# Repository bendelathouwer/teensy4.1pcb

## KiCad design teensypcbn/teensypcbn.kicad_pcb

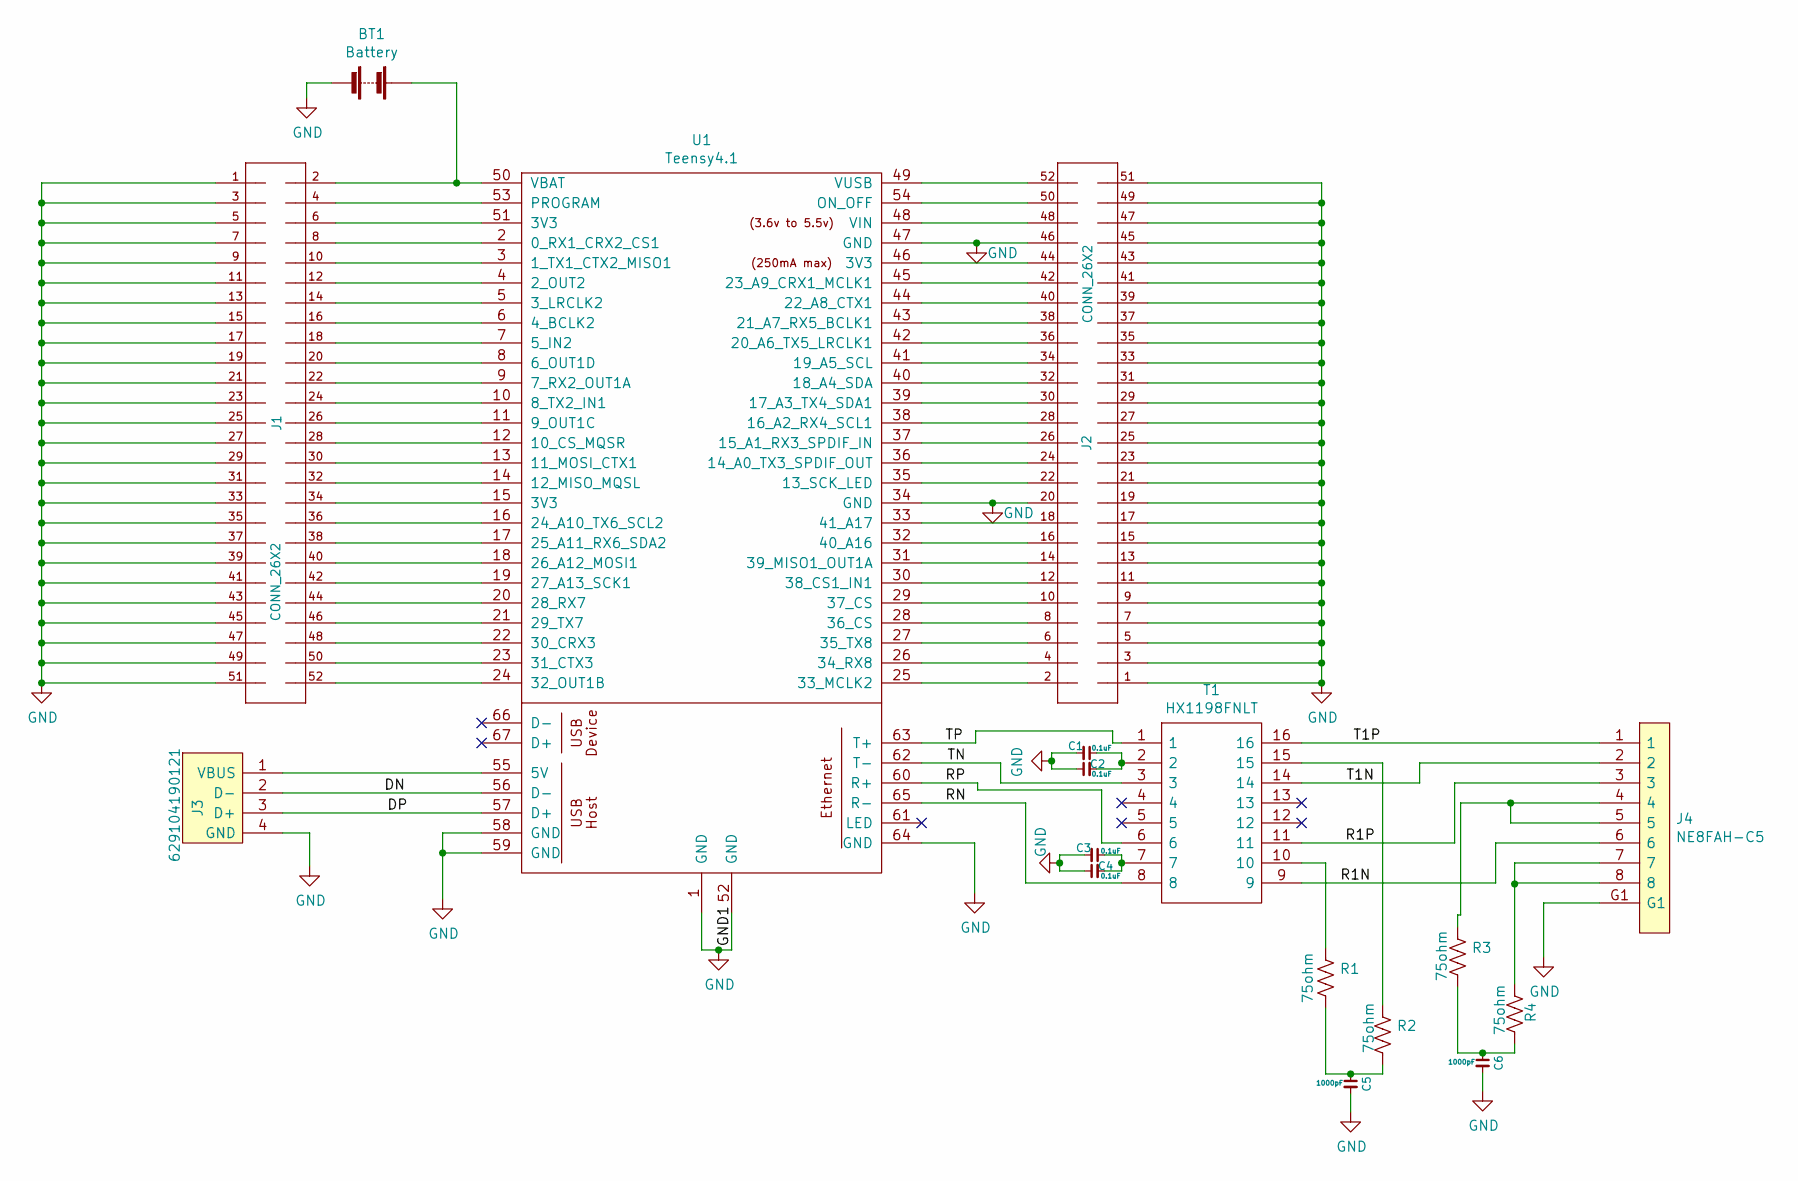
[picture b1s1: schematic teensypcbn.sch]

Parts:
BT1: Battery; JST_PH_B2B-PH-SM4-TB_1x02-1MP_P2.00mm_Vertical
C1, C2, C3, C4: 0.1uF; C_0603_1608Metric_Pad0.99x1.00mm_HandSolder
C5, C6: 1000pF; C_0603_1608Metric_Pad0.99x1.00mm_HandSolder
J1, J2: CONN_26X2; PinHeader_2x26_P2.54mm_Vertical
J3: 629104190121; Mouser Part Number 710-629104190121
J4: NE8FAH-C5; NE8FAHC5; Mouser Part Number 568-NE8FAH-C5
R1, R2, R3, R4: 75ohm; R_0603_1608Metric
T1: HX1198FNLT; Manufacturer_Part_Number HX1198FNLT; Mouser Part Number 673-HX1198FNLT
U1: Teensy4.1; Teensy41

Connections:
/DN: J3.2 (D-), U1.56 (D-)
/DP: J3.3 (D+), U1.57 (D+)
/R1N: J4.6, T1.9
/R1P: J4.3, T1.11
/RN: T1.8, U1.65 (R-)
/RP: T1.6, U1.60 (R+)
/T1N: J4.2, T1.14
/T1P: J4.1, T1.16
/TN: T1.3, U1.62 (T-)
/TP: T1.1, U1.63 (T+)
GND: BT1.2 (-), C1.2, C2.1, C3.2, C4.1, C5.2, C6.2, J1.1, J1.3, J1.5, J1.7, J1.9, J1.11, J1.13, J1.15, J1.17, J1.19, J1.21, J1.23, J1.25, J1.27, J1.29, J1.31, J1.33, J1.35, J1.37, J1.39, J1.41, J1.43, J1.45, J1.47, J1.49, J1.51, J2.1, J2.3, J2.5, J2.7, J2.9, J2.11, J2.13, J2.15, J2.17, J2.19, J2.20, J2.21, J2.23, J2.25, J2.27, J2.29, J2.31, J2.33, J2.35, J2.37, J2.39, J2.41, J2.43, J2.45, J2.46, J2.47, J2.49, J2.51, J3.4 (GND), J4.G1, U1.1 (GND), U1.34 (GND), U1.47 (GND), U1.52 (GND), U1.58 (GND), U1.59 (GND), U1.64 (GND)
unnamed: BT1.1 (+), J1.2, U1.50 (VBAT)
unnamed: C1.1, C2.2, T1.2
unnamed: C3.1, C4.2, T1.7
unnamed: C5.1, R1.2, R2.2
unnamed: C6.1, R3.2, R4.2
unnamed: J1.4, U1.53 (PROGRAM)
unnamed: J1.6, U1.51 (3V3)
unnamed: J1.8, U1.2 (0_RX1_CRX2_CS1)
unnamed: J1.10, U1.3 (1_TX1_CTX2_MISO1)
unnamed: J1.12, U1.4 (2_OUT2)
unnamed: J1.14, U1.5 (3_LRCLK2)
unnamed: J1.16, U1.6 (4_BCLK2)
unnamed: J1.18, U1.7 (5_IN2)
unnamed: J1.20, U1.8 (6_OUT1D)
unnamed: J1.22, U1.9 (7_RX2_OUT1A)
unnamed: J1.24, U1.10 (8_TX2_IN1)
unnamed: J1.26, U1.11 (9_OUT1C)
unnamed: J1.28, U1.12 (10_CS_MQSR)
unnamed: J1.30, U1.13 (11_MOSI_CTX1)
unnamed: J1.32, U1.14 (12_MISO_MQSL)
unnamed: J1.34, U1.15 (3V3)
unnamed: J1.36, U1.16 (24_A10_TX6_SCL2)
unnamed: J1.38, U1.17 (25_A11_RX6_SDA2)
unnamed: J1.40, U1.18 (26_A12_MOSI1)
unnamed: J1.42, U1.19 (27_A13_SCK1)
unnamed: J1.44, U1.20 (28_RX7)
unnamed: J1.46, U1.21 (29_TX7)
unnamed: J1.48, U1.22 (30_CRX3)
unnamed: J1.50, U1.23 (31_CTX3)
unnamed: J1.52, U1.24 (32_OUT1B)
unnamed: J2.2, U1.25 (33_MCLK2)
unnamed: J2.4, U1.26 (34_RX8)
unnamed: J2.6, U1.27 (35_TX8)
unnamed: J2.8, U1.28 (36_CS)
unnamed: J2.10, U1.29 (37_CS)
unnamed: J2.12, U1.30 (38_CS1_IN1)
unnamed: J2.14, U1.31 (39_MISO1_OUT1A)
unnamed: J2.16, U1.32 (40_A16)
unnamed: J2.18, U1.33 (41_A17)
unnamed: J2.22, U1.35 (13_SCK_LED)
unnamed: J2.24, U1.36 (14_A0_TX3_SPDIF_OUT)
unnamed: J2.26, U1.37 (15_A1_RX3_SPDIF_IN)
unnamed: J2.28, U1.38 (16_A2_RX4_SCL1)
unnamed: J2.30, U1.39 (17_A3_TX4_SDA1)
unnamed: J2.32, U1.40 (18_A4_SDA)
unnamed: J2.34, U1.41 (19_A5_SCL)
unnamed: J2.36, U1.42 (20_A6_TX5_LRCLK1)
unnamed: J2.38, U1.43 (21_A7_RX5_BCLK1)
unnamed: J2.40, U1.44 (22_A8_CTX1)
unnamed: J2.42, U1.45 (23_A9_CRX1_MCLK1)
unnamed: J2.44, U1.46 (3V3)
unnamed: J2.48, U1.48 (VIN)
unnamed: J2.50, U1.54 (ON_OFF)
unnamed: J2.52, U1.49 (VUSB)
unnamed: J3.1 (VBUS), U1.55 (5V)
unnamed: J4.4, J4.5, R3.1
unnamed: J4.7, J4.8, R4.1
unnamed: R1.1, T1.10
unnamed: R2.1, T1.15

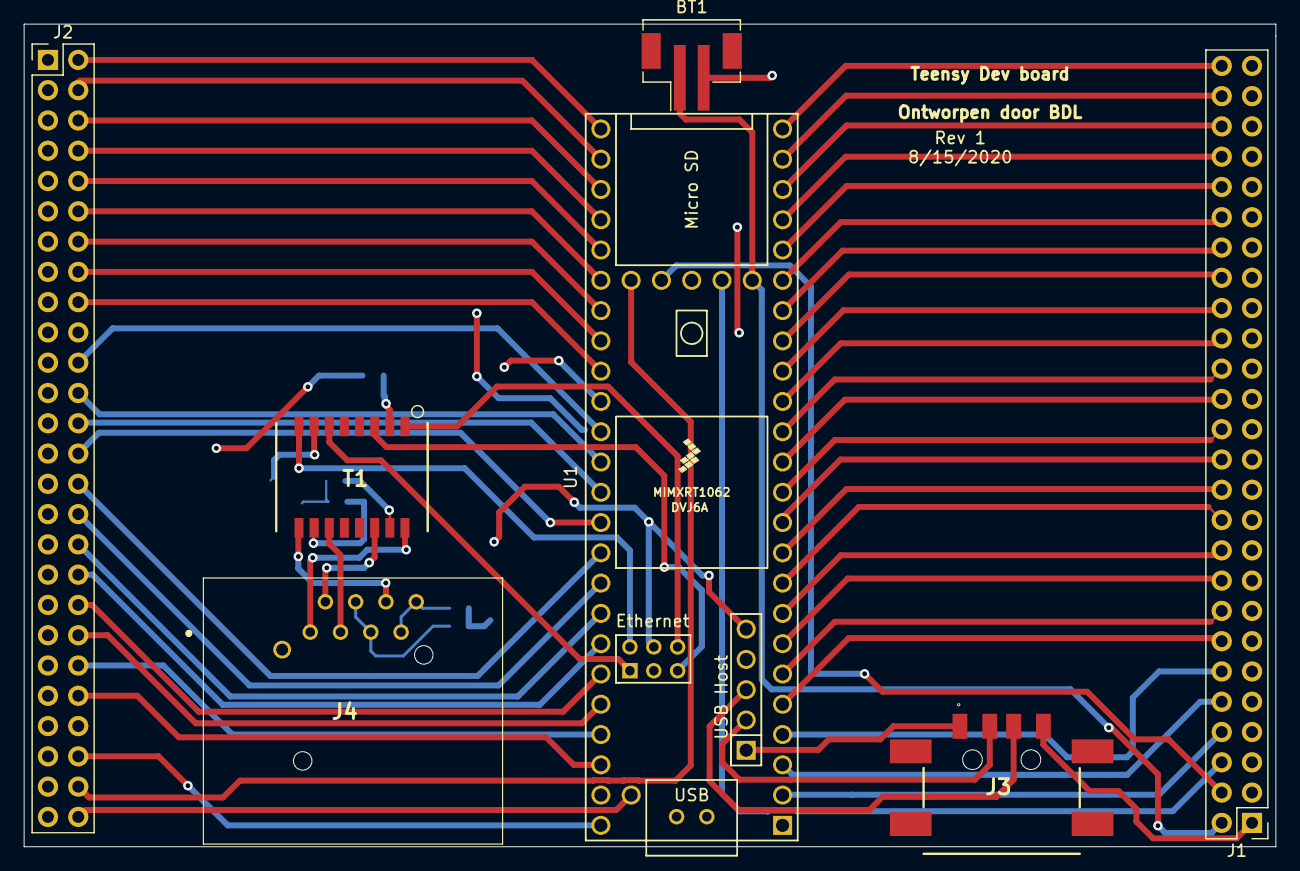
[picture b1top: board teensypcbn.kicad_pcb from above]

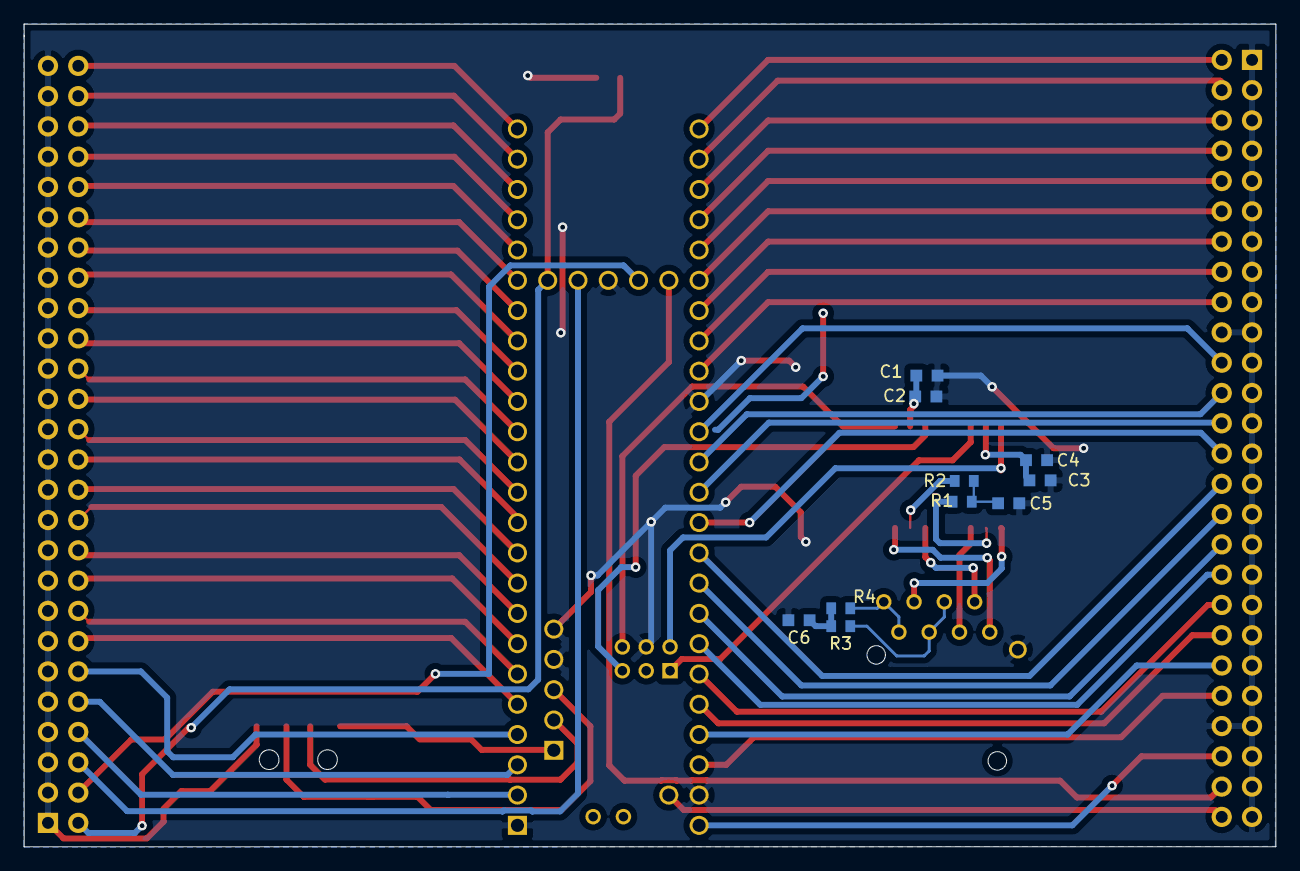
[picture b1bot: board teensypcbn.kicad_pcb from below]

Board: 2 copper layers, 105.0 x 69.0 mm, 17 parts (10 on the bottom side), 70 nets.

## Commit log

2020-07-05 ethernet en usb
    ethernet en usb toegevoegd
2020-07-05 schema
    schema voledig klaar
2020-07-06 routing
    routing begonnen
2020-07-06 pcb
    ethernet en usb nog te routen
2020-07-06 routing V2
    routing gestart met de juiste connector
2020-07-07 placment
    placment bijna klaar
2020-07-07 bijna klaar
    bijna klaar met routen
2020-07-07 routing klaar
    routing klaar , bom moet nog aangepast worden
2020-08-15 fab files
    fabrication files toegevoegd
